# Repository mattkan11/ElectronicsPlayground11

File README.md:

# ElectronicsPlayground11

Here are the specifications for the files :

Heart-shaped LED Chaser(PCB_github).jpg : JPEG picture of the PCB circuit for Heart-shaped LED Chaser board.

Heart-shaped LED Chaser(Schematics_github).jpg : JPEG picture of the Schematic Diagram for Heart-shaped LED Chaser board.

Heart-shaped-LED.brd : PCB circuit for Heart-shaped LED Chaser board drawn with EagleCAD.

Heart-shaped-LED.sch : Schematic Diagram for Heart-shaped LED Chaser board drawn with EagleCAD.

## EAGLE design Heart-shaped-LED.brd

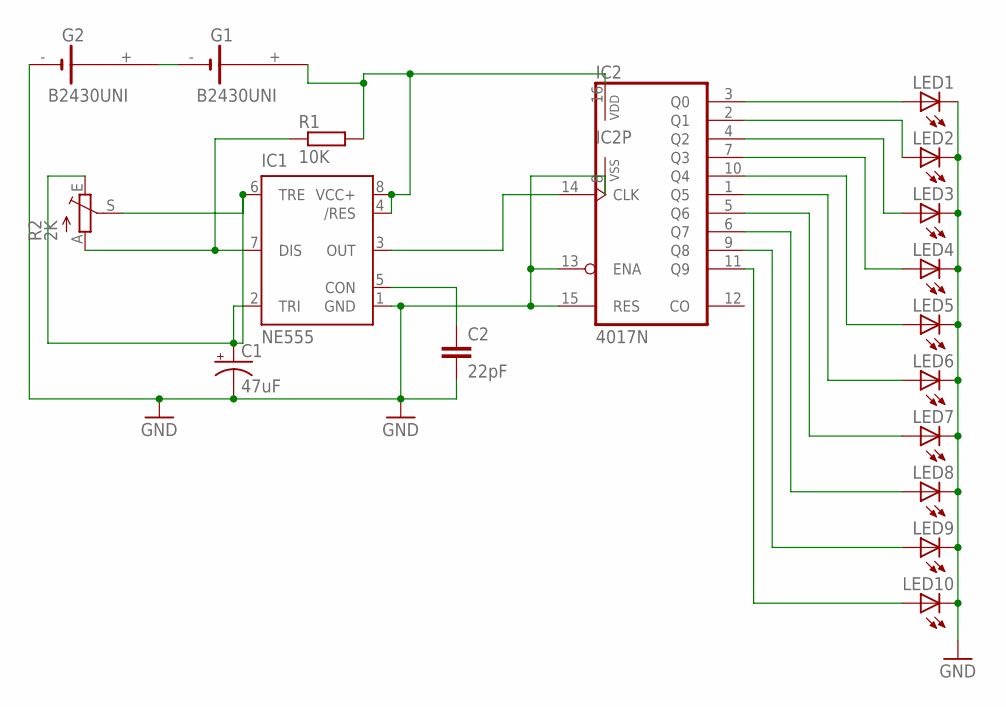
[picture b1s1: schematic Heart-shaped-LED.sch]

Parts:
C1: 47uF; B45181A
C2: 22pF; C025-024X044
G1, G2: B2430UNI
IC1: NE555; DIL-08
IC2: 4017N; DIL16
LED1, LED2, LED3, LED4, LED5, LED6, LED7, LED8, LED9, LED10: LED5MM
R1: 10K; 0207/7
R2: 2K; CA9V

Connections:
GND: C1.-, C2.2, G2.-, IC1.1 (GND), IC2.8 (VSS), IC2.13 (ENA), IC2.15 (RES), LED1.K (C), LED2.K (C), LED3.K (C), LED4.K (C), LED5.K (C), LED6.K (C), LED7.K (C), LED8.K (C), LED9.K (C), LED10.K (C)
unnamed: IC1.3 (OUT), IC2.14 (CLK)
unnamed: G1.+, IC1.4 (/RES), IC1.8 (VCC+), IC2.16 (VDD), R1.2
unnamed: IC2.3 (Q0), LED1.A
unnamed: IC1.7 (DIS), R1.1, R2.A
unnamed: C1.+, IC1.2 (TRI), IC1.6 (TRE), R2.E, R2.S
unnamed: C2.1, IC1.5 (CON)
unnamed: IC2.2 (Q1), LED2.A
unnamed: IC2.4 (Q2), LED3.A
unnamed: IC2.7 (Q3), LED4.A
unnamed: IC2.10 (Q4), LED5.A
unnamed: IC2.1 (Q5), LED6.A
unnamed: IC2.5 (Q6), LED7.A
unnamed: IC2.6 (Q7), LED8.A
unnamed: IC2.9 (Q8), LED9.A
unnamed: IC2.11 (Q9), LED10.A
unnamed: G1.-, G2.+

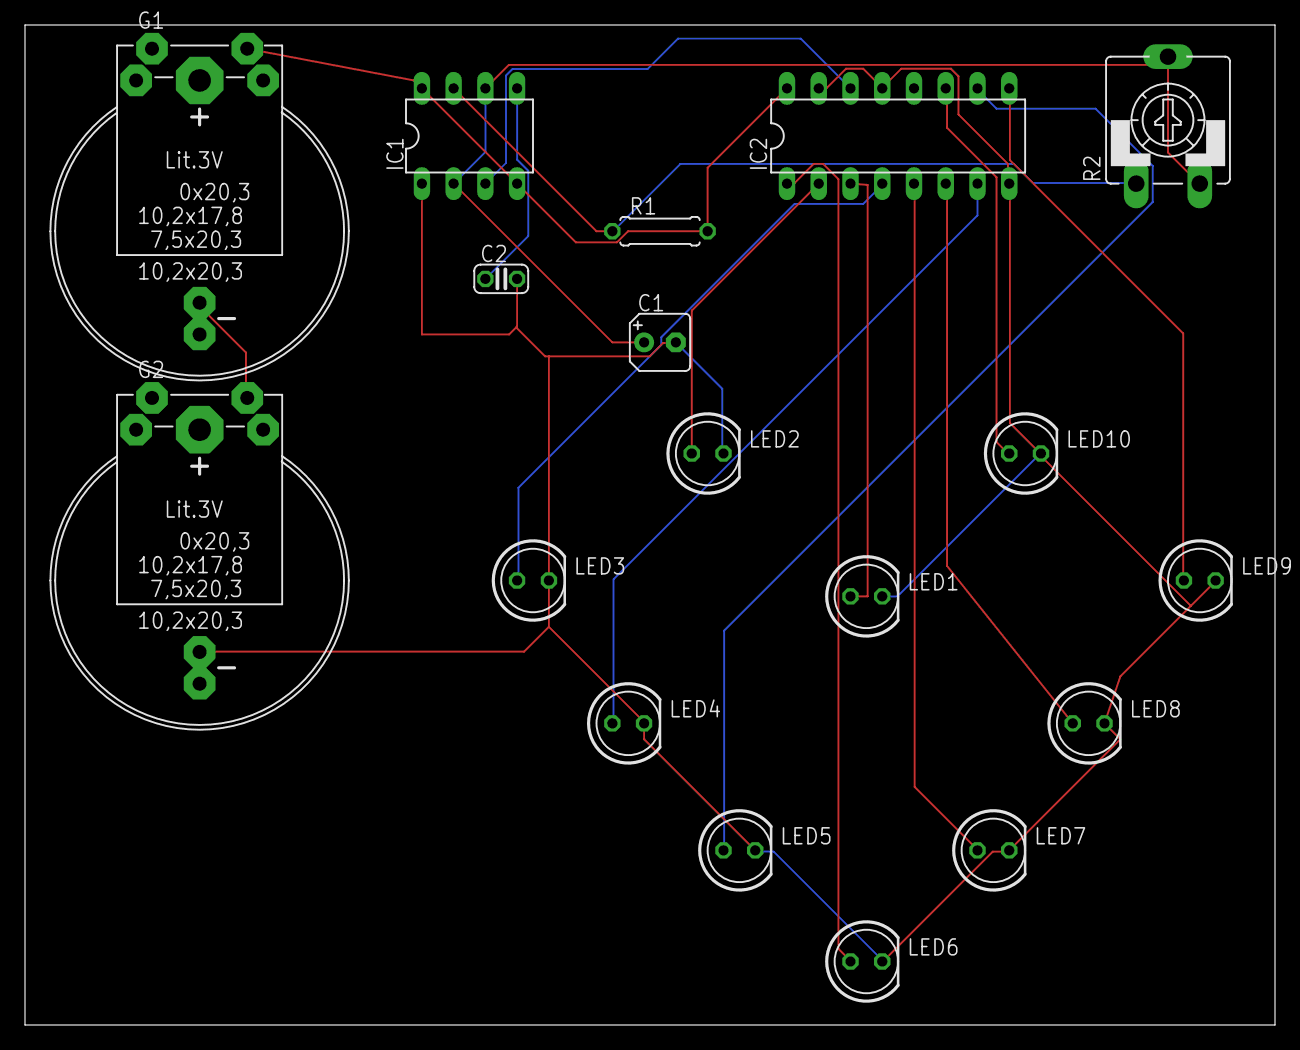
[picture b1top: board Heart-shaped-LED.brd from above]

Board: 2 copper layers, 100.0 x 80.0 mm, 18 parts (0 on the bottom side), 17 nets.

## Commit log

2019-01-24 Create Heart-shaped LED Chaser PCB Board
2019-04-04 Create DIY PCB for Electronic Password Locker
